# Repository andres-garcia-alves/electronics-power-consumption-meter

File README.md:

# Power Consumption Meter

A power consumption meter based on Arduino Nano.  
This project is a **work-in-progress**.

Two PCB versions are provided:
- Version A - With Battery Holder
- Version B - Without Battery Holder

&nbsp;

This project use the following electronic components:
- 01 x Double sided copper clad board (9x10cms)
- 01 x Arduino UNO / 01 x Arduino Nano v3
- 01 x Arduino socket (optional, 2x15)
- 01 x INA219 module
- 01 x INA219 socket (optional, 1x6)
- 01 x Display 5641BS, 7-segment, 4 digit, common anode
- 01 x Display socket (optional, 2x6)
- 11 x 470 ohm resistors
- 03 x LED diodes
- 01 x Rocker Button (optional, power on/off) / 01 x Jumper
- 01 x Switch Slide Button (power source selector)
- 01 x Switch Push Button (measure selector)
- 01 x 18650 (x2) batery holder / 01 x 9V Batery holder
- 01 x DC-jack connector (optional, externar power 5-12V)
- 01 x USB Type-A connector pair (male/female)
- 01 x USB Type-B Mini connector pair (male/female)
- 01 x USB Type-B Micro connector pair (male/female)
- 02 x DC connector-pair (male/female)
- 01 x Bornier 4-pin / 01 x JST conector 4-pin
- 04 x Bornier 2-pin / 02 x JST conector 2-pin

How to use:
- Conect this gadget between the device to measure and its power source.
- Pressing the push-button changes the measure tu display: voltage (V), consumption (mA), or total power (mW).

Features:
- Power input: 7-12V
- Measurements: 0-26V @3.2A (max)
- Accuracy: 0.01V, ~1mA, ~1mW

Notes:
- Measure only one device at a time, all power connectors intenally uses a common bus.
- Internal connections:
  - USB-A: power + data
  - USB-B mini/micro: power-only
  - DC-Jacks: power-only

&nbsp;

### Screenshots

| Breadboard                                      | Assembly                                        |
|-------------------------------------------------|-------------------------------------------------|
|              |                |

| Version A - Schematics Diagram                  | Version A - PCB Diagram                         |
|-------------------------------------------------|-------------------------------------------------|
|         |                |

| Version A - PCB Render 3D                       | Version A - PCB Render 3D                       |
|-------------------------------------------------|-------------------------------------------------|
|     |      |

| Version B - PCB Render 3D                       | Version B - PCB Render 3D                       |
|-------------------------------------------------|-------------------------------------------------|
|     |      |

| Case 3D Model                                   | Project Final                                   |
|-------------------------------------------------|-------------------------------------------------|
|              |              |

See 'Rescources' sub-folder for more pictures & videos of the project.

&nbsp;

### Version History

v1.0 (2025.12.20) - Initial release.  
v1.1 (2025.12.21) - Version A: adding PCB schematics and layout.  
v1.2 (2025.12.22) - Version A: update PCB schematics and layout, adding firmware base code.  
v1.3 (2025.12.23) - Version A: update PCB schematics and layout, update firmware.  
v1.4 (2025.12.25) - Version B: adding PCB schematics and layout.  
v1.5 (2025.12.26) - Version A: adding case 3D model, adding 'Stickers' folder.  
v1.6 (2025.12.29) - Adding PCB building and assembly pictures.  
v1.7 (2026.01.27) - Version B: adding case 3D model.  
v1.8 (2026.02.11) - Version B: minor case 3D model improvements.  
v1.9 (2026.02.12) - Update 'README.md'.  

&nbsp;

This source code is licensed under GPL v3.0  
Please send me your feedback about this project: andres.garcia.alves@gmail.com

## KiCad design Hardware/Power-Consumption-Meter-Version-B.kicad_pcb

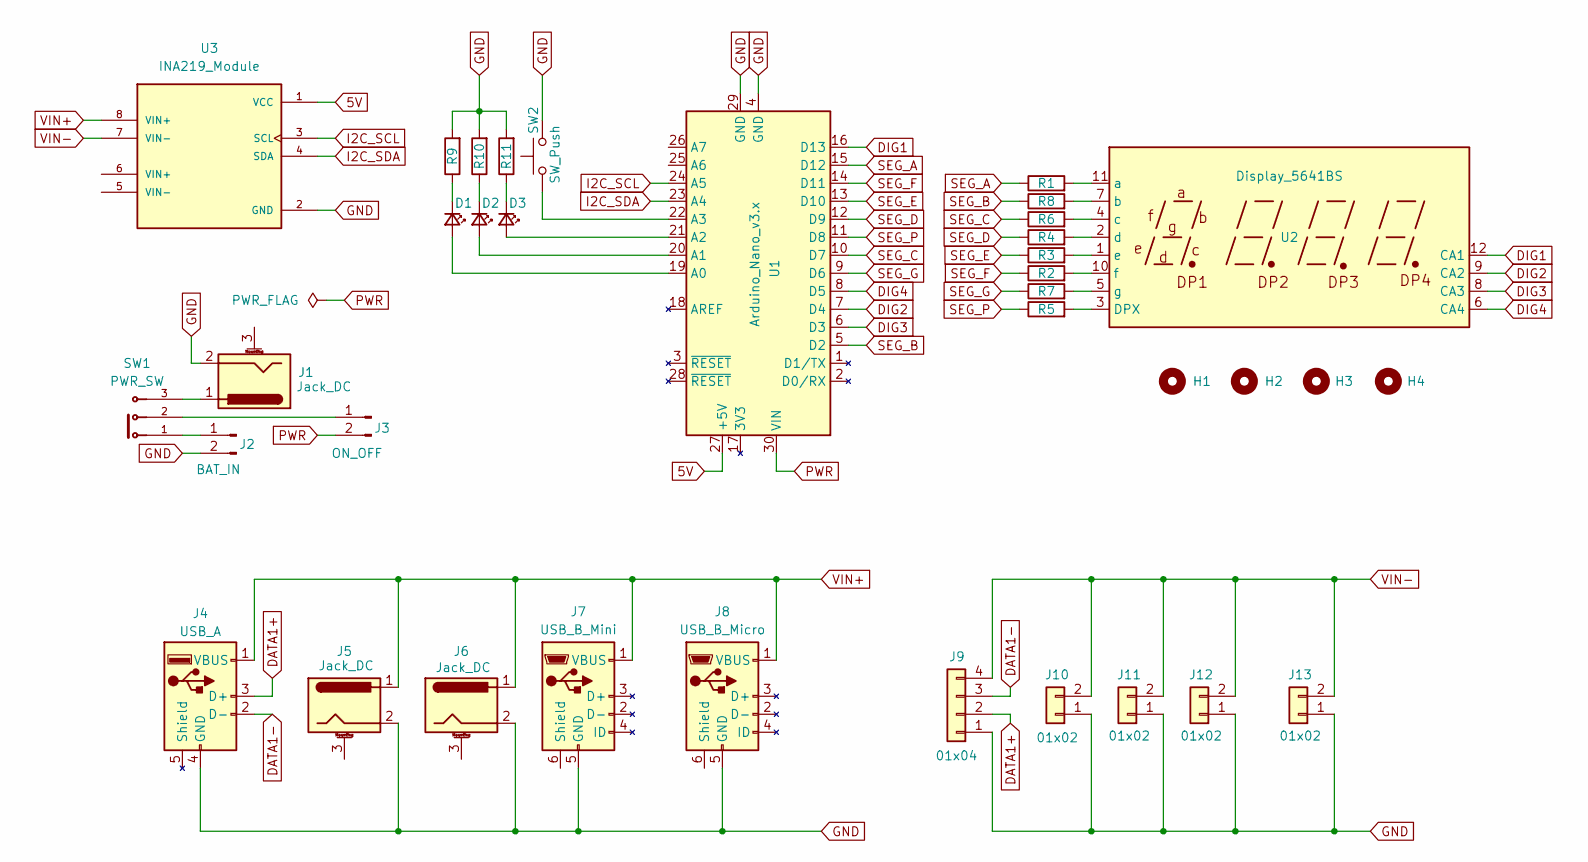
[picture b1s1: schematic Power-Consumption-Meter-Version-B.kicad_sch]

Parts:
D1, D2, D3: LED; LED_D3.0mm
H1, H2, H3, H4: MountingHole; MountingHole_2mm
J1, J5, J6: Jack_DC; BarrelJack_Horizontal
J2: BAT_IN; PinHeader_1x02_P2.54mm_Vertical
J3: ON_OFF; PinHeader_1x02_P2.54mm_Vertical
J4: USB_A; USB_A_Molex_67643_Horizontal
J7: USB_B_Mini; USB_B_Mini_OTG_THT_Molex_548190519
J8: USB_B_Micro; USB_B_Micro_THT_Amphenol_101181940011LF
J9: 01x04; JST_EH_B4B-EH-A_1x04_P2.50mm_Vertical
J10, J11, J12, J13: 01x02; JST_EH_B2B-EH-A_1x02_P2.50mm_Vertical
R1, R2, R3, R4, R5, R6, R7, R8, R9, R10, R11: R470; R_Axial_DIN0207_L6.3mm_D2.5mm_P2.54mm_Vertical
SW1: PWR_SW; Switch_Slide_SPDT_Straight_TE_1825159_1
SW2: SW_Push; SW_PUSH-12mm_Wuerth-430476085716
U1: Arduino_Nano_v3.x; Arduino_Nano_v3
U2: Display_5641BS; CA56-12CGKWA
U3: INA219_Module; INA219_Module_Generic

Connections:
5V: U1.27 (+5V), U3.1 (VCC)
DATA1+: J4.3 (D+), J9.2
DATA1-: J4.2 (D-), J9.3
DIG1: U1.16 (D13), U2.12 (CA1)
DIG2: U1.7 (D4), U2.9 (CA2)
DIG3: U1.6 (D3), U2.8 (CA3)
DIG4: U1.8 (D5), U2.6 (CA4)
GND: J1.2, J2.2, J4.4 (GND), J5.2, J6.2, J7.5 (GND), J8.5 (GND), J9.1, J10.1, J11.1, J12.1, J13.1, R9.2, R10.2, R11.2, SW2.2, U1.4 (GND), U1.29 (GND), U3.2 (GND)
I2C_SCL: U1.24 (A5), U3.3 (SCL)
I2C_SDA: U1.23 (A4), U3.4 (SDA)
unnamed: D1.2 (A), U1.19 (A0)
unnamed: D1.1 (K), R9.1
unnamed: D2.2 (A), U1.20 (A1)
unnamed: D2.1 (K), R10.1
unnamed: D3.2 (A), U1.21 (A2)
unnamed: D3.1 (K), R11.1
unnamed: J1.1, SW1.3
unnamed: J2.1, SW1.1
unnamed: J3.1, SW1.2
unnamed: SW2.1, U1.22 (A3)
unnamed: R5.2, U2.3 (DPX)
unnamed: R1.2, U2.11 (a)
unnamed: R8.2, U2.7 (b)
unnamed: R6.2, U2.4 (c)
unnamed: R4.2, U2.2 (d)
unnamed: R3.2, U2.1 (e)
unnamed: R2.2, U2.10 (f)
unnamed: R7.2, U2.5 (g)
PWR: J3.2, U1.30 (VIN)
SEG_A: R1.1, U1.15 (D12)
SEG_B: R8.1, U1.5 (D2)
SEG_C: R6.1, U1.10 (D7)
SEG_D: R4.1, U1.12 (D9)
SEG_E: R3.1, U1.13 (D10)
SEG_F: R2.1, U1.14 (D11)
SEG_G: R7.1, U1.9 (D6)
SEG_P: R5.1, U1.11 (D8)
VIN+: J4.1 (VBUS), J5.1, J6.1, J7.1 (VBUS), J8.1 (VBUS), U3.8 (VIN+)
VIN-: J9.4, J10.2, J11.2, J12.2, J13.2, U3.7 (VIN-)

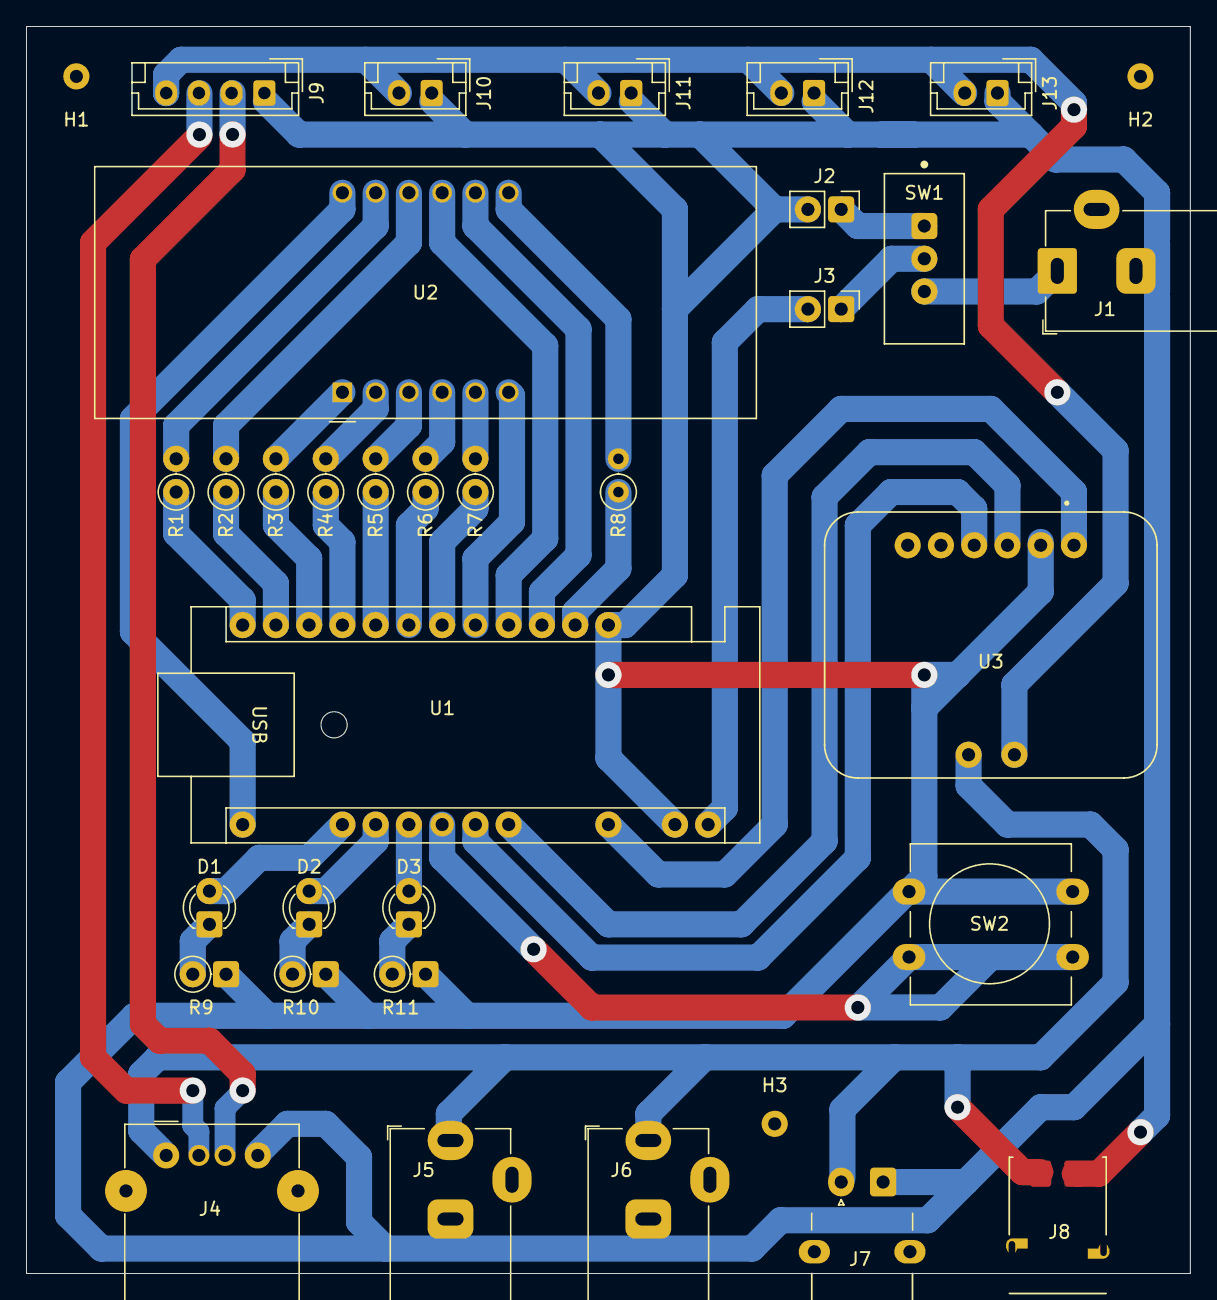
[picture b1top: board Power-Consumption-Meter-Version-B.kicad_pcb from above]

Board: 2 copper layers, 88.9 x 95.2 mm, 36 parts (0 on the bottom side), 39 nets.

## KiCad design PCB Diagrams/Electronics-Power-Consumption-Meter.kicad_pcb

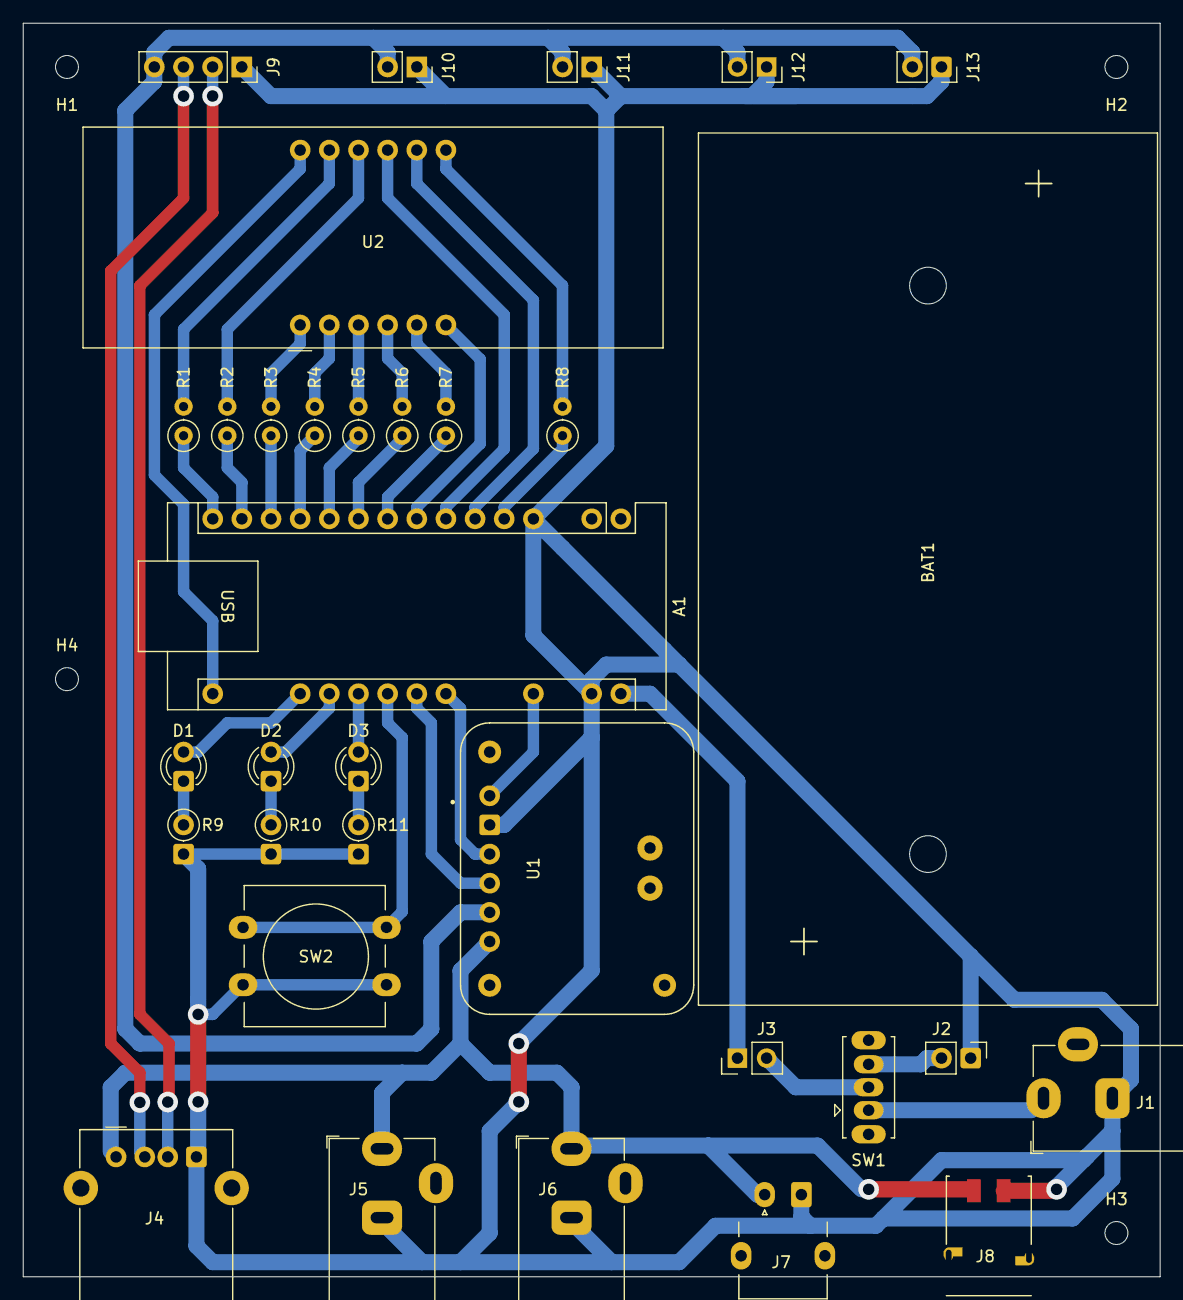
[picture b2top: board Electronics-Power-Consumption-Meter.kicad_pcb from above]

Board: 2 copper layers, 99.1 x 109.2 mm, 37 parts (0 on the bottom side), 39 nets.

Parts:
A1: Arduino_Nano_v3.x; Arduino_Nano_v3
BAT1: BAT_18650; BatteryHolder_18650_X2
D1, D2, D3: LED; LED_D3.0mm
H1, H2, H3, H4: MountingHole; MountingHole_2mm
J1, J5, J6: Jack_DC; BarrelJack_Horizontal
J2, J3: 01x02; PinHeader_1x02_P2.54mm_Vertical
J4: USB_A; USB_A_Molex_67643_Horizontal
J7: USB_B_Mini; USB_B_Mini_OTG_THT_Molex_548190519
J8: USB_B_Micro; USB_B_Micro_THT_Amphenol_101181940011LF
J9: 01x04; PinSocket_1x04_P2.54mm_Vertical
J10, J11, J12, J13: 01x02; PinSocket_1x02_P2.54mm_Vertical
R1, R2, R3, R4, R5, R6, R7, R8, R9, R10, R11: R470; R_Axial_DIN0207_L6.3mm_D2.5mm_P2.54mm_Vertical
SW1: SW_SPDT; SW_Slide_SPDT_Straight_CK_OS102011MS2Q
SW2: SW_Push; SW_PUSH-12mm_Wuerth-430476085716
U1: INA219_Module; INA219_Module_Adafruit
U2: Display_5641BS; CA56-12CGKWA

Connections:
5V: A1.27 (+5V), U1.1 (VCC)
DATA1+: J4.3 (D+), J9.2
DATA1-: J4.2 (D-), J9.3
DIG1: A1.16 (D13), U2.12 (CA1)
DIG2: A1.7 (D4), U2.9 (CA2)
DIG3: A1.6 (D3), U2.8 (CA3)
DIG4: A1.8 (D5), U2.6 (CA4)
GND: A1.4 (GND), A1.29 (GND), J1.2, J2.1, J4.4 (GND), J5.2, J6.2, J7.5 (GND), J8.5 (GND), J9.1, J10.1, J11.1, J12.1, J13.1, R9.2, R10.2, R11.2, SW2.2, U1.2 (GND)
I2C_SCL: A1.24 (A5), U1.3 (SCL)
I2C_SDA: A1.23 (A4), U1.4 (SDA)
unnamed: A1.19 (A0), D1.2 (A)
unnamed: A1.20 (A1), D2.2 (A)
unnamed: A1.21 (A2), D3.2 (A)
unnamed: A1.22 (A3), SW2.1
unnamed: J2.2, SW1.3 (C)
unnamed: D1.1 (K), R9.1
unnamed: D2.1 (K), R10.1
unnamed: D3.1 (K), R11.1
unnamed: J3.2, SW1.2 (B)
unnamed: J1.1, SW1.1 (A)
unnamed: R5.2, U2.3 (DPX)
unnamed: R1.2, U2.11 (a)
unnamed: R8.2, U2.7 (b)
unnamed: R6.2, U2.4 (c)
unnamed: R4.2, U2.2 (d)
unnamed: R3.2, U2.1 (e)
unnamed: R2.2, U2.10 (f)
unnamed: R7.2, U2.5 (g)
PWR: A1.30 (VIN), J3.1
SEG_A: A1.15 (D12), R1.1
SEG_B: A1.14 (D11), R2.1
SEG_C: A1.10 (D7), R6.1
SEG_D: A1.12 (D9), R4.1
SEG_E: A1.13 (D10), R3.1
SEG_F: A1.5 (D2), R8.1
SEG_G: A1.9 (D6), R7.1
SEG_P: A1.11 (D8), R5.1
VIN+: J4.1 (VBUS), J5.1, J6.1, J7.1 (VBUS), J8.1 (VBUS), U1.6 (VIN+)
VIN-: J9.4, J10.2, J11.2, J12.2, J13.2, U1.5 (VIN-)

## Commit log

2025-12-22 adding schematics and PCB
2025-12-23 update schematics+pcb, add firmware code
2025-12-23 update firmware
2025-12-23 update schematics and PCB
2025-12-25 Adding PCB version 2 without baterry holder
2025-12-26 Adding case 3D model
2025-12-26 Adding 'Stikers' folder
2025-12-26 Adding case 3D model, adding 'Stickers' folder
2025-12-29 update PCB connectors
2025-12-29 Adding PCB building and assembly pictures
2026-01-28 Version B: adding case 3D model
2026-02-02 Update Tracks
2026-02-10 minor case 3D model improvements
2026-02-12 Update 'README.md'
